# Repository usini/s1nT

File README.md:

# s1nT : A 4-Voice Polyphonic Synthetizer for Arduino

```
          _          ______
         /' \        /\__  _\
    ____/\_, \    ___\/_/\ \/
   /',__\/_/\ \ /' _ `\ \ \ \
  /\__, `\ \ \ \/\ \/\ \ \ \ \
  \/\____/  \ \_\ \_\ \_\ \ \_\
   \/___/    \/_/\/_/\/_/  \/_/
````
Based on the_synth by dzlonline : https://github.com/dzlonline/the_synth

# Libraries Used:
* AceButton : https://github.com/bxparks/AceButton
* the_synth : https://github.com/dzlonline/the_synth

# Schematics

# Demo

https://www.youtube.com/watch?v=24HnNLr4qp4   

Présentation du montage en version Breadboard FR : https://www.youtube.com/watch?v=l1WhdirNEj4

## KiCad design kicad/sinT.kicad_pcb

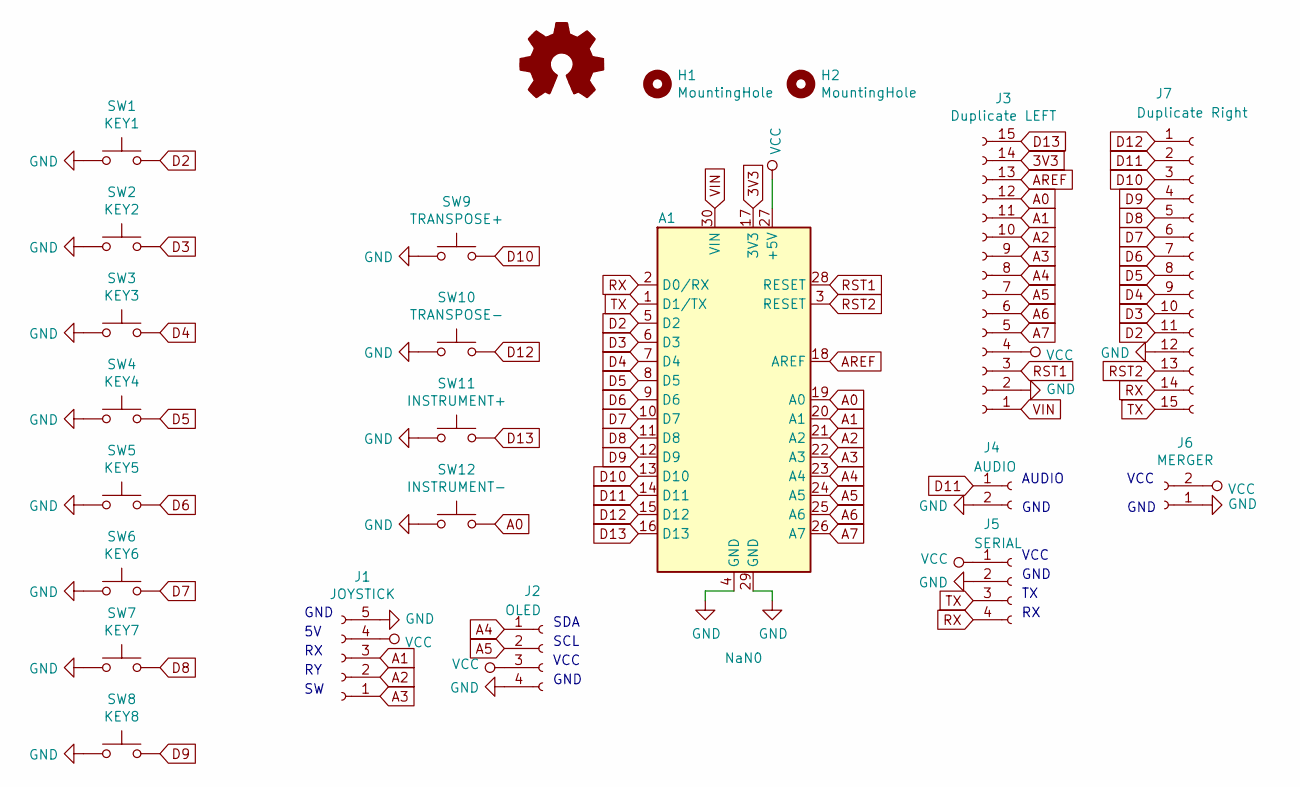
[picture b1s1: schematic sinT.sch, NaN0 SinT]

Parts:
A1: NaN0; Arduino_Nano
H1, H2: MountingHole; MountingHole_3.2mm_M3
J1: JOYSTICK; PinSocket_1x05_P2.54mm_Vertical
J2: OLED; PinHeader_1x04_P2.54mm_Vertical
J3: Duplicate LEFT; PinSocket_1x15_P2.54mm_Vertical
J4: AUDIO; PinSocket_1x02_P2.54mm_Vertical
J5: SERIAL; PinSocket_1x04_P2.54mm_Vertical
J6: MERGER; PinSocket_1x02_P2.54mm_Vertical
J7: Duplicate Right; PinSocket_1x15_P2.54mm_Vertical
SW1: KEY1; SW_PUSH_6mm_H7.3mm
SW2: KEY2; SW_PUSH_6mm_H7.3mm
SW3: KEY3; SW_PUSH_6mm_H7.3mm
SW4: KEY4; SW_PUSH_6mm_H7.3mm
SW5: KEY5; SW_PUSH_6mm_H7.3mm
SW6: KEY6; SW_PUSH_6mm_H7.3mm
SW7: KEY7; SW_PUSH_6mm_H7.3mm
SW8: KEY8; SW_PUSH_6mm_H7.3mm
SW9: TRANSPOSE+; SW_PUSH_6mm_H7.3mm
SW10: TRANSPOSE-; SW_PUSH_6mm_H7.3mm
SW11: INSTRUMENT+; SW_PUSH_6mm_H7.3mm
SW12: INSTRUMENT-; SW_PUSH_6mm_H7.3mm

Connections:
3V3: A1.17 (3V3), J3.14
A0: A1.19 (A0), J3.12, SW12.2
A1: A1.20 (A1), J1.3, J3.11
A2: A1.21 (A2), J1.2, J3.10
A3: A1.22 (A3), J1.1, J3.9
A4: A1.23 (A4), J2.1, J3.8
A5: A1.24 (A5), J2.2, J3.7
A6: A1.25 (A6), J3.6
A7: A1.26 (A7), J3.5
AREF: A1.18 (AREF), J3.13
D2: A1.5 (D2), J7.11, SW1.2
D3: A1.6 (D3), J7.10, SW2.2
D4: A1.7 (D4), J7.9, SW3.2
D5: A1.8 (D5), J7.8, SW4.2
D6: A1.9 (D6), J7.7, SW5.2
D7: A1.10 (D7), J7.6, SW6.2
D8: A1.11 (D8), J7.5, SW7.2
D9: A1.12 (D9), J7.4, SW8.2
D10: A1.13 (D10), J7.3, SW9.2
D11: A1.14 (D11), J4.1, J7.2
D12: A1.15 (D12), J7.1, SW10.2
D13: A1.16 (D13), J3.15, SW11.2
GND: A1.4 (GND), A1.29 (GND), J1.5, J2.4, J3.2, J4.2, J5.2, J6.1, J7.12, SW1.1, SW2.1, SW3.1, SW4.1, SW5.1, SW6.1, SW7.1, SW8.1, SW9.1, SW10.1, SW11.1, SW12.1
RST1: A1.28 (RESET), J3.3
RST2: A1.3 (RESET), J7.13
RX: A1.2 (D0/RX), J5.4, J7.14
TX: A1.1 (D1/TX), J5.3, J7.15
VCC: A1.27 (+5V), J1.4, J2.3, J3.4, J5.1, J6.2
VIN: A1.30 (VIN), J3.1

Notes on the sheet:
SDA
SCL
VCC
GND
AUDIO

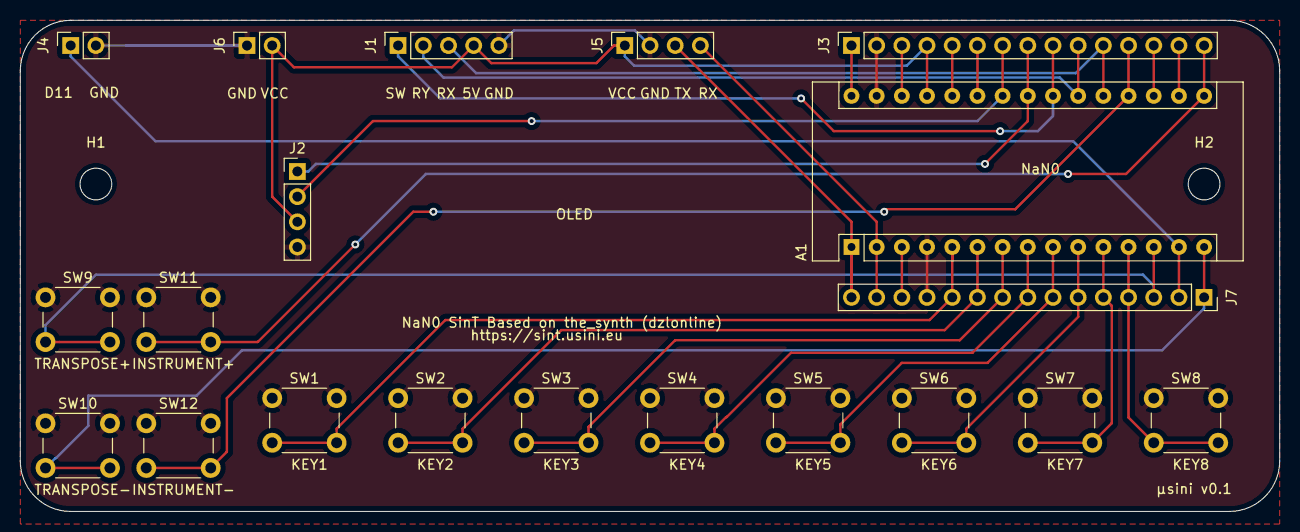
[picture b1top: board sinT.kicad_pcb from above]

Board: 2 copper layers, 127.0 x 49.5 mm, 22 parts (0 on the bottom side), 29 nets.

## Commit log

2020-01-20 add thumbnail / schematics
2020-01-20 Add comments in s1nt.ino
2020-01-21 Disable pitch/modulation by default
2020-01-29 Add more recent demo in readme
2020-01-29 Wrong pins / add photos
